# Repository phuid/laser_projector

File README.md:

# Raspberry Pi RGB laser projector
A vector laser projector with an easy to understand UI.\
UI includes:
- integrated display control with a rotary encoder,
- web server on the local network
- discord bot accesible when the RPi is online

## table of contents
- [Raspberry Pi RGB laser projector](#raspberry-pi-rgb-laser-projector)
  - [table of contents](#table-of-contents)
  - [thesis](#thesis)
  - [how to install](#how-to-install)
  - [supported projection file formats](#supported-projection-file-formats)
  - [hw](#hw)
    - [galvos](#galvos)
      - [DAC - mcp4822](#dac---mcp4822)
      - [amps - TL082](#amps---tl082)
    - [laser](#laser)
    - [LCD + encoder](#lcd--encoder)
  - [sw](#sw)
    - [communication](#communication)
    - [lasershow](#lasershow)
    - [UI](#ui)
    - [web\_ui](#web_ui)
    - [discord\_bot](#discord_bot)
    - [wifi\_manager](#wifi_manager)
    - [comms format](#comms-format)
      - [lasershow comms](#lasershow-comms)
        - [basic commands:](#basic-commands)
        - [responses:](#responses)
      - [wifi\_manager comms](#wifi_manager-comms)

## thesis
I wrote a whole thesis in [czech](https://en.wikipedia.org/wiki/Czech_Republic) language about this project. It is available in [this repository](https://github.com/phuid/laser_projector-thesis) [(direct link to the pdf file)](https://github.com/phuid/laser_projector-thesis/blob/master/text.pdf).

## how to install

```bash
git clone https://github.com/phuid/laser_projector.git
cd laser_projector
bash install.sh
```
this script installs all the dependencies of my programs and sets up the RaspberryPi to start all the programs on boot using [pm2](https://pm2.keymetrics.io/).

## supported projection file formats
The projector can read and project **.ild** and (much more popular) **.svg** file formats.
**.ild** files can be generated using specialised software like [laserworld showeditor](https://www.showeditor.com/en).
**.svg** files from any editor are internally converted to **.ild** using [this svg2ild.py script](https://github.com/marcan/openlase/blob/master/tools/svg2ild.py) from [gh/marcan/openlase](https://github.com/marcan/openlase)

## hw
My plans include battery power, usually galvos come with a power supply and powering the laser isn't that hard using a step-up. My module takes around 0.45A @ 9V. Make sure you dont brick your pi by taking its power. Raspberry Pis often don't take it well when an undervoltage occurs on their 5V line and they certainly aren't made to power anything more than an LED from their 3.3V PS.

### galvos
take -10 to +10V differential signal between to lines (base and inverted),
The DAC + opamps circuit which generates this signal is nicely described in [this article](https://www.instructables.com/Arduino-Laser-Show-With-Real-Galvos/).
My implemetation of it in kicad files can be found in [pcb/kicad](pcb/kicad).

#### DAC - mcp4822
DAC controlled by the RPi creates an analog signal between 0 and 5V.

#### amps - TL082
TL082 from texas instruments, each channel has one chip, each chip has two op amps.
One opamp inverts and modifies the signal based on the potenciometers (getting the inverted ILDA signal),
Second opamp inverts it again for the base ILDA signal

### laser
rgb laser module from https://www.laserlands.net/diode-laser-module/rgb-combined-white-laser-module/11010003.html
requires 8.5-12V power
takes 35kHz TTL / PWM on 3 pins, these pins are connected directly to the raspberry pi

pin connections between the laser module and RPi
|LASER|RPi|
|---|---|
|red|GPIO22|
|green|GPIO27|
|blue|GPIO17|

### LCD + encoder
Any 20x4 LCD with an I2C backpack + any rotary encoder with a button 
LCD connections:
|LCD|RPi|
|---|---|
|Vcc|5V|
|GND|GND|
|SCK|GPIO3|
|SDA|GPIO2|
|backlight|GPIO18|

encoder connections:
|encoder|RPi|
|---|---|
|A|GPIO5|
|common|GND|
|B|GPIO6|
|button1|GND|
|button1|GPIO13|

## sw
2 backend programs (lasershow *(c++)* + wifi_manager *(node.js)*) and 3 frontend programs (UI *(c++)* + web_ui *(node.js)* + discord_bot *(node.js)*)

### communication
each backend has its pub/sub sockets
lasershow publishes to `tcp://localhost:5556` and receives commands from `tcp://localhost:5556`
wifi_manager publishes to `tcp://localhost:5558` and receives commands from `tcp://localhost:5559`

### lasershow
- backend program that takes care of the actual projecting through controlling the galvos and the laser module

### UI
- allows control of backend programs through the built-in LCD and encoder

### web_ui
- allows control of backend programs through a web interface available on the local network

### discord_bot
- allows control of backend programs through a discord bot

### wifi_manager
- allows switching between three modes of wifi:
  - wifi off (`stealth`)
  - wifi on (`wifi`) -- RPi wifi on and trying to connect to known nearby networks
  - access point (`hotspot`) -- RPi wifi on transmitting its own wifi which other devices can connect to

### comms format
#### lasershow comms

lasershow executable takes commands **from all UI processes** through a **ZeroMQ TCP socket**
command format
`COMMAND` + ` ` + `ARG1` + ` ` + `ARG2` + ` ` + ` ` + `ARG4`
-> parse with a simple while loop lol no need for fancy functions

##### basic commands:
any process can send a command into the socket and all processes will read responses from lasershow executable
- `PROJECT` args: `<filename>`
  - `<filename>` must have extension `.ild`<!-- or `.lpc`(laserprojector_custom) --> otherwise error `INVALID_ARG`
- `STOP` (no args)
- `PAUSE` (no args)
- `GAME` args: `<game_name>`
  - `game_name` is any of the following ``//TODO: game names (not yes implemented)
- `PRESS` (no args), only handled if game is running
- `RELEASE` (no args), only handled if game is running
- `OPTION` args: `<mode>` `<option_name>` `<value>`
  - `mode`: any of `write`/`read`/`reset`
  - `option_name`: any of the following
    - `progress`
    - `current_frame` - if a projection is active, this will seek to the defined frame of the projection, must not exceed number_of_frames (every pos info gives this argument)
    - `point_delay`
    - `target_frame_time`
    - `repeat`
    - `trapeziod_horizontal`
    - `trapeziod_vertical`
  - `value` only read when using `write` parameter

##### responses:
lasershow exec can write to the socket at any time
- `ERROR: <e> <details>`:
  - `e`: any of the following; returned if received command couldn't be parsed correctly
    - `E2BIG`: too many arguments (option read/reset command probably includes value argument)
    - `EINVAL`: invalid argument (typo in argument or project filename probably has wrong extension)
    - `ENOENT`: file doesn't exist
    - `INVALID_CMD`: probably typo in a command
    - `OTHER`
  - `details`: if error type supports it, details will be included
- there is no success message
- `INFO: <details>`
  - details - one of following:
    - `OPTION <name> <val>`
      - name: name of option being changed; *any of*:
        - `point_delay`
        - `repeat`
        - `target_frame_time`
        - `trapezoid_horizontal`
        - `trapezoid_vertical`
      - val: numeric (float) value of the option
    - `STOP`
    - `PAUSE <val>`
      - val: 1 - paused, 0 - not paused
    - `PROJECT <filename>`
      - filename: filename of the file being projected
    - `POS <pos> OF <max>`
      - pos: position of coursor in projected file
      - max: size of projected file
- `DISPLAY: <text>`: client shall display text to the user and hide it when a new command comes or when user sees it
- `ALERT: <text>`: client shall display text to the user and only hide it and process following commands after user sees the alert

#### wifi_manager comms
takes following commands
- `read`: prints out following parameters:
  - `wifi_setting: <stealth|wifi|hotspot>`
  - `wifi_ssid: <SSID>`: SSID as returned by `iwgetid --raw` or `iw dev` in case hotspot is active
  - `mode_raw: <MODE_RAW>`: MODE_RAW (0-7) as returned by `iwgetid --mode --raw`
  - `mode: <MODE>`: MODE based on MODE_RAW; possible outputs: `Auto|Ad-Hoc|Managed|Master|Repeater|Secondary|Monitor|Unknown/bug`

- `write <stealth|wifi|hotspot>`
  - `stealth`: wifi off
  - `wifi`: connect to nearby known networks
  - `hotspot`: create new network, raspberry pi becomes the access point

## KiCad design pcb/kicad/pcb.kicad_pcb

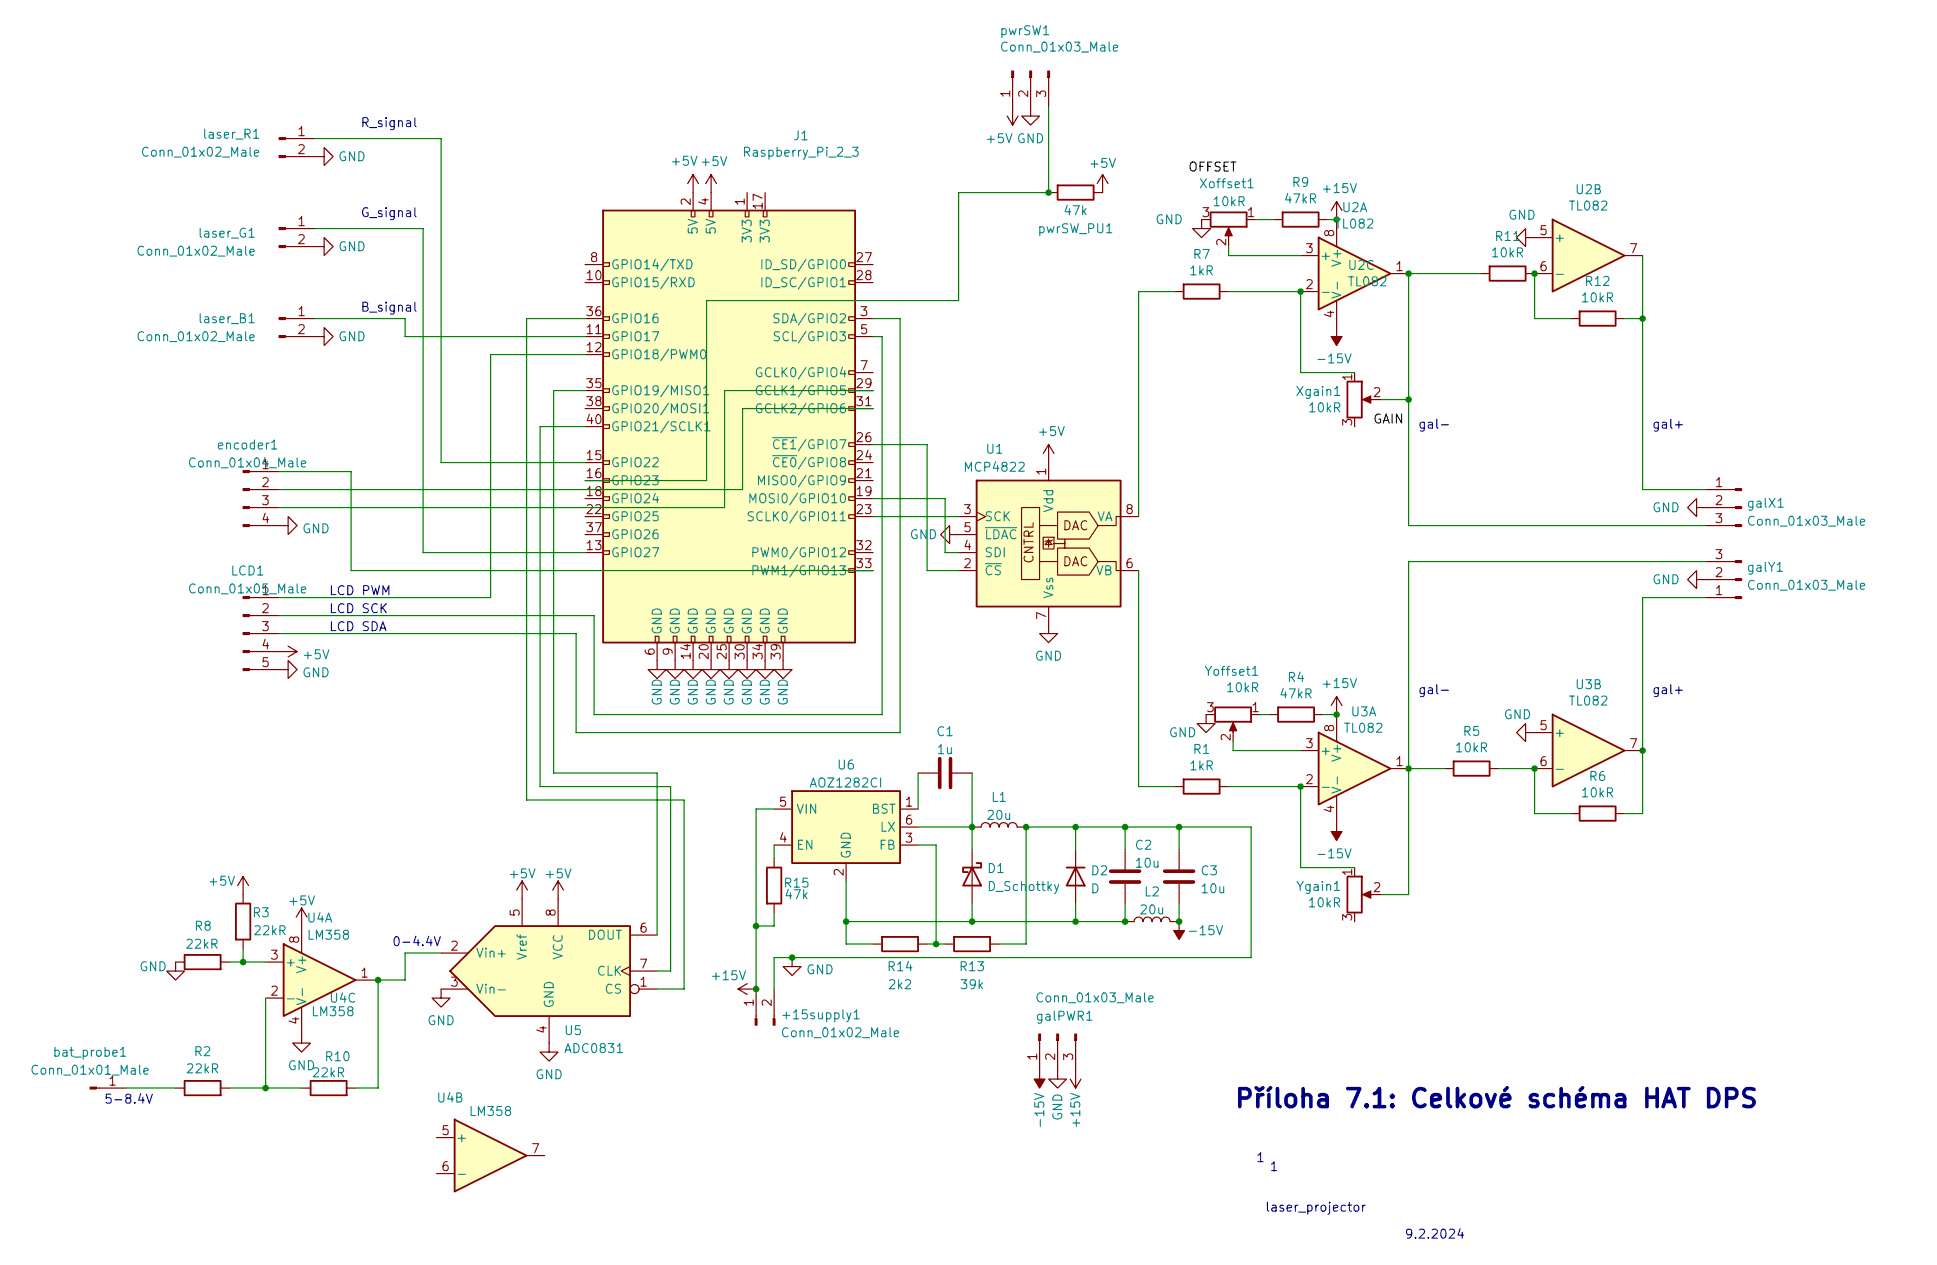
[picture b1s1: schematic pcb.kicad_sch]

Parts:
+15supply1: Conn_01x02_Male; PinHeader_1x02_P2.54mm_Horizontal
C1: 1u; C_Disc_D5.0mm_W2.5mm_P5.00mm
C2, C3: 10u; CP_Radial_D5.0mm_P2.00mm
D1: D_Schottky; D_SMC_Handsoldering
D2: D; D_SMC_Handsoldering
J1: Raspberry_Pi_2_3; PinSocket_2x20_P2.54mm_Vertical
L1, L2: 20u; L_Sumida_CR75
LCD1: Conn_01x05_Male; PinHeader_1x05_P2.54mm_Horizontal
R1, R7: 1kR; R_1812_4532Metric_Pad1.30x3.40mm_HandSolder
R2, R3, R8, R10: 22kR; R_1812_4532Metric_Pad1.30x3.40mm_HandSolder
R4, R9: 47kR; R_1812_4532Metric_Pad1.30x3.40mm_HandSolder
R5, R6, R11, R12: 10kR; R_1812_4532Metric_Pad1.30x3.40mm_HandSolder
R13: 39k; R_1812_4532Metric_Pad1.30x3.40mm_HandSolder
R14: 2k2; R_1812_4532Metric_Pad1.30x3.40mm_HandSolder
R15: 47k; R_1812_4532Metric_Pad1.30x3.40mm_HandSolder
U1: MCP4822; DIP-8_W7.62mm
U2, U3: TL082; DIP-8_W7.62mm
U4: LM358; DIP-8_W7.62mm
U5: ADC0831; DIP-8_W7.62mm
U6: AOZ1282CI; SOT-23-6
Xgain1: 10kR; Potentiometer_Alps_RK09K_Single_Vertical
Xoffset1: 10kR; Potentiometer_Alps_RK09K_Single_Vertical
Ygain1: 10kR; Potentiometer_Alps_RK09K_Single_Vertical
Yoffset1: 10kR; Potentiometer_Alps_RK09K_Single_Vertical
bat_probe1: Conn_01x01_Male; PinHeader_1x01_P2.54mm_Horizontal
encoder1: Conn_01x04_Male; PinHeader_1x04_P2.54mm_Horizontal
galPWR1: Conn_01x03_Male; PinHeader_1x03_P2.54mm_Horizontal
galX1: Conn_01x03_Male; PinHeader_1x03_P2.54mm_Horizontal
galY1: Conn_01x03_Male; PinHeader_1x03_P2.54mm_Horizontal
laser_B1: Conn_01x02_Male; PinHeader_1x02_P2.54mm_Horizontal
laser_G1: Conn_01x02_Male; PinHeader_1x02_P2.54mm_Horizontal
laser_R1: Conn_01x02_Male; PinHeader_1x02_P2.54mm_Horizontal
pwrSW1: Conn_01x03_Male; PinHeader_1x03_P2.54mm_Horizontal
pwrSW_PU1: 47k; R_1812_4532Metric_Pad1.30x3.40mm_HandSolder

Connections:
+5V: J1.2 (5V), J1.4 (5V), LCD1.4, R3.1, U1.1 (Vdd), U4.8 (V+), U5.5 (Vref), U5.8 (VCC), pwrSW1.1, pwrSW_PU1.1
+15V: +15supply1.1, R4.1, R9.1, R15.2, U2.8 (V+), U3.8 (V+), U6.5 (VIN), galPWR1.3
-15V: C3.2, L2.2, U2.4 (V-), U3.4 (V-), galPWR1.1
GND: +15supply1.2, C2.1, C3.1, D2.1 (K), J1.6 (GND), J1.9 (GND), J1.14 (GND), J1.20 (GND), J1.25 (GND), J1.30 (GND), J1.34 (GND), J1.39 (GND), L1.2, LCD1.5, R8.1, R13.1, U1.5 (~LDAC), U1.7 (Vss), U2.5 (+), U3.5 (+), U4.4 (V-), U5.3 (Vin-), U5.4 (GND), Xoffset1.3, Yoffset1.3, encoder1.4, galPWR1.2, galX1.2, galY1.2, laser_B1.2, laser_G1.2, laser_R1.2, pwrSW1.2
unnamed: C2.2, D1.2 (A), D2.2 (A), L2.1, R14.2, U6.2 (GND)
unnamed: C1.1, D1.1 (K), L1.1, U6.6 (LX)
unnamed: J1.29 (GCLK1/GPIO5), encoder1.3
unnamed: J1.31 (GCLK2/GPIO6), encoder1.2
unnamed: J1.36 (GPIO16), U5.1 (CS)
unnamed: J1.11 (GPIO17), laser_B1.1
unnamed: J1.12 (GPIO18/PWM0), LCD1.1
unnamed: J1.35 (GPIO19/MISO1), U5.6 (DOUT)
unnamed: J1.40 (GPIO21/SCLK1), U5.7 (CLK)
unnamed: J1.15 (GPIO22), laser_R1.1
unnamed: J1.16 (GPIO23), pwrSW1.3, pwrSW_PU1.2
unnamed: J1.13 (GPIO27), laser_G1.1
unnamed: J1.19 (MOSI0/GPIO10), U1.4 (SDI)
unnamed: J1.33 (PWM1/GPIO13), encoder1.1
unnamed: J1.23 (SCLK0/GPIO11), U1.3 (SCK)
unnamed: J1.5 (SCL/GPIO3), LCD1.2
unnamed: J1.3 (SDA/GPIO2), LCD1.3
unnamed: J1.26 (~CE1/GPIO7), U1.2 (~CS)
unnamed: R4.2, Yoffset1.1
unnamed: R9.2, Xoffset1.1
unnamed: R7.2, U1.8 (VA)
unnamed: R1.2, U1.6 (VB)
unnamed: U2.3 (+), Xoffset1.2
unnamed: R7.1, U2.2 (-), Xgain1.1
unnamed: R11.1, R12.2, U2.6 (-)
unnamed: U3.3 (+), Yoffset1.2
unnamed: R1.1, U3.2 (-), Ygain1.1
unnamed: R5.1, R6.2, U3.6 (-)
unnamed: R3.2, R8.2, U4.3 (+)
unnamed: R2.2, R10.1, U4.2 (-)
unnamed: R10.2, U4.1, U5.2 (Vin+)
unnamed: C1.2, U6.1 (BST)
unnamed: R15.1, U6.4 (EN)
unnamed: R13.2, R14.1, U6.3 (FB)
unnamed: R2.1, bat_probe1.1
unnamed: R12.1, U2.7, galX1.1
unnamed: R11.2, U2.1, Xgain1.2, galX1.3
unnamed: R6.1, U3.7, galY1.1
unnamed: R5.2, U3.1, Ygain1.2, galY1.3

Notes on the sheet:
Příloha 7.1: Celkové schéma HAT DPS
LCD SCK
G_signal
0-4.4V
LCD PWM
gal-
9.2.2024
B_signal
LCD SDA
laser_projector
R_signal
gal+
5-8.4V

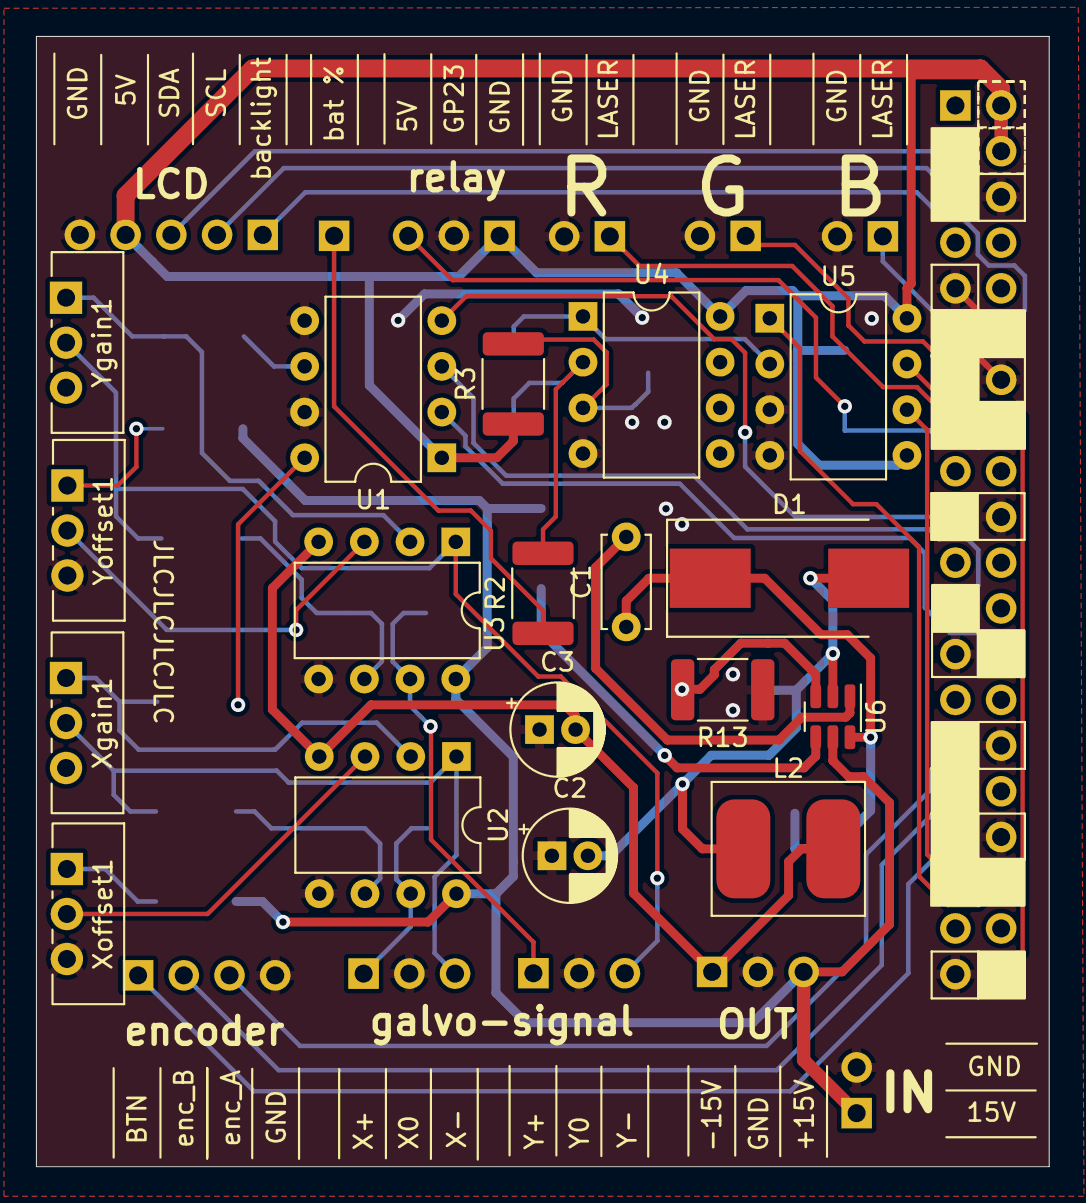
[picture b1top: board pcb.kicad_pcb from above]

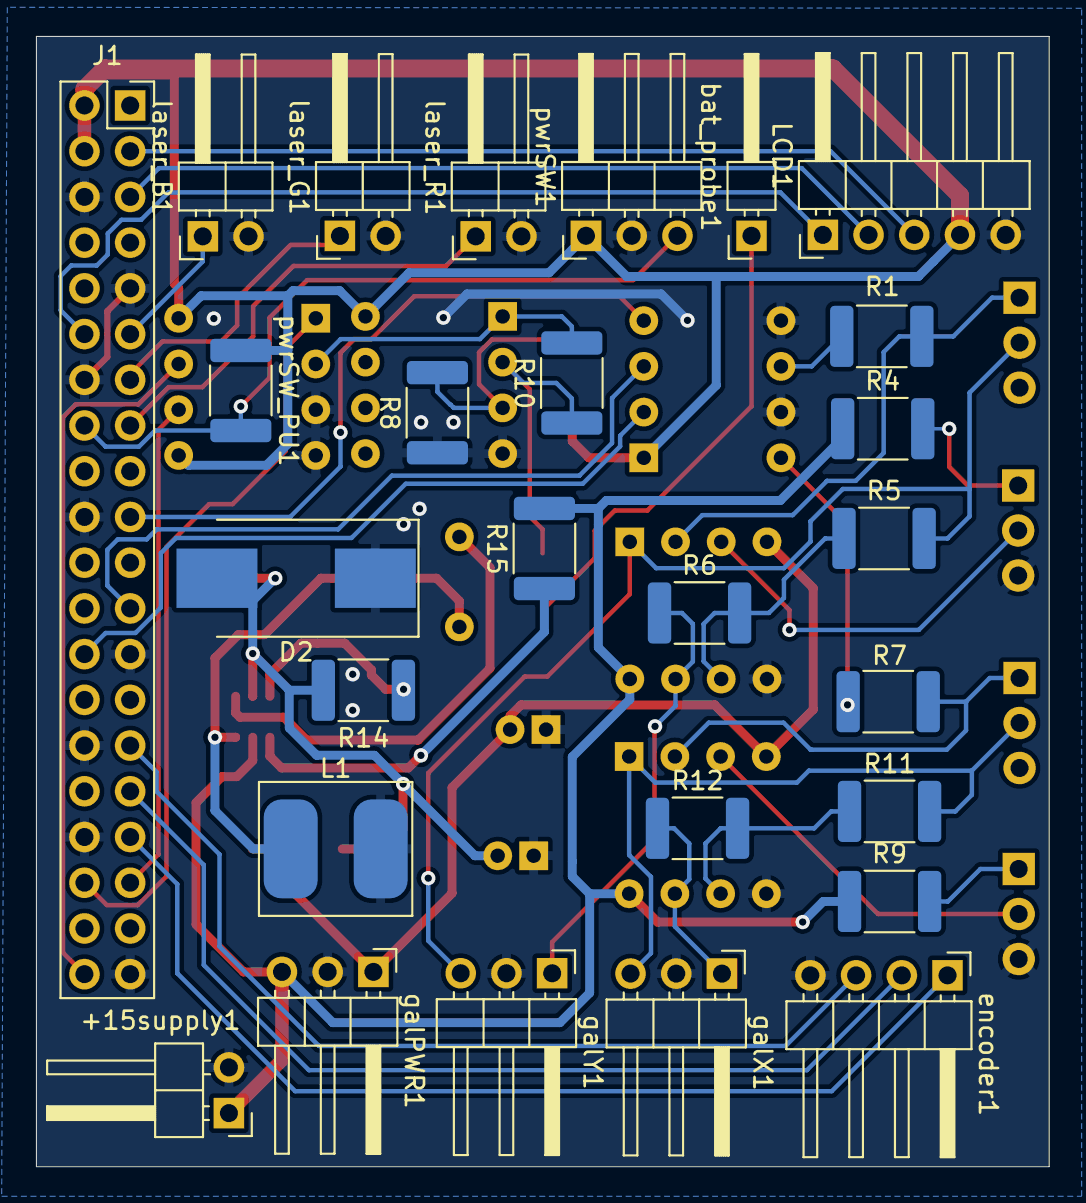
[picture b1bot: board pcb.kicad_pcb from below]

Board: 2 copper layers, 56.3 x 62.8 mm, 45 parts (27 on the bottom side), 43 nets.

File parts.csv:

### Footprint positions - created on Fri Jan 26 19:06:12 2024 ###,,,,,,,
### Printed by KiCad version 7.0.10,,,,,,,
## Unit = mm, Angle = deg.,,,,,,
## Side : both lol,,,,,,,
Ref, Val, Link, Package, PosX, PosY, Rot, Side
C1, 1u, https://www.gme.cz/v/1486151/hitano-ck-1u-50v-x7r-rm508-10-k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, C_Disc_D5.0mm_W2.5mm_P5.00mm,258.572,-54.3668,90, top
C2, 10u,https://www.gme.cz/v/1489492/hitano-ce-10u-63vit-hit-exr-5x1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, CP_Radial_D5.0mm_P2.00mm,254.4419,-67.0814,0, top
C3, 10u,, CP_Radial_D5.0mm_P2.00mm,253.7561,-60.071,0, top
D1, D_Schottky, https://www.gme.cz/v/1493653/ss56c-schottkyho-dioda, D_SMC_Handsoldering,267.6398,-51.6636,0, top
D2, D,, D_SMC_Handsoldering,-267.6398,-51.6636,0, bottom
U1, MCP4822,bought, DIP-8_W7.62mm,248.3258,-44.9734,180, top
U2, TL082,bought, DIP-8_W7.62mm,249.1386,-61.5696,-90, top
U3, TL082,bought, DIP-8_W7.62mm,249.1032,-49.6416,-90, top
U4, LM358,https://www.gme.cz/v/1487661/texas-instruments-lm358p, DIP-8_W7.62mm,256.169,-37.1194,0, top
U5, ADC0831,https://www.gme.cz/v/1490502/texas-instruments-adc0831ccn-nopb, DIP-8_W7.62mm,266.5476,-37.221,0, top
U6, AOZ1282CI,https://www.tme.eu/cz/en/details/aoz1282ci/voltage-regulator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, SOT-23-6,270.05,-59.3598,-90, top
J1, Raspberry_Pi_2_3,bought, PinSocket_2x20_P2.54mm_Vertical,-276.86,-25.4,180, bottom
L1, 20u,https://www.gme.cz/v/1496226/da105np-220m-tlumivka-smd, L_Sumida_CR75,-265.4446,-66.7004,180, bottom
L2, 20u,, L_Sumida_CR75,267.5782,-66.7004,0, top
R2, R,https://www.gme.cz/v/1485408/yageo-r1206-22k-025w-1-smd-rezistor, R_1812_4532Metric_Pad1.30x3.40mm_HandSolder,253.9492,-52.5018,90, top
R3, R,, R_1812_4532Metric_Pad1.30x3.40mm_HandSolder,252.2982,-40.8686,90, top
R8, R,, R_1812_4532Metric_Pad1.30x3.40mm_HandSolder,-259.7912,-42.4688,90, bottom
R10, R,, R_1812_4532Metric_Pad1.30x3.40mm_HandSolder,-252.3236,-40.8178,90, bottom
R13, 39k,https://www.gme.cz/v/1485560/yageo-r1206-39k-025w-1-smd-rezistor, R_1812_4532Metric_Pad1.30x3.40mm_HandSolder,263.9314,-57.8612,180, top
R1, 1kR,https://www.gme.cz/v/1485383/yageo-r1206-1k-025w-1-smd-rezistor, R_1812_4532Metric_Pad1.30x3.40mm_HandSolder,-235.1024,-38.227,0, bottom
R7, 1kR,, R_1812_4532Metric_Pad1.30x3.40mm_HandSolder,-234.7468,-58.5216,0, bottom
R4, 47kR,https://www.gme.cz/v/1483907/yageo-r1206-47k-025w-1-smd-rezistor, R_1812_4532Metric_Pad1.30x3.40mm_HandSolder,-235.0516,-43.3578,180, bottom
R9, 47kR,, R_1812_4532Metric_Pad1.30x3.40mm_HandSolder,-234.6706,-69.6214,180, bottom
R15, 47kR,, R_1812_4532Metric_Pad1.30x3.40mm_HandSolder,-253.8476,-50.0126,90, bottom
pwrSW_PU1, 47kR,, R_1812_4532Metric_Pad1.30x3.40mm_HandSolder,-270.7132,-41.2344,-90, bottom
R5, 10kR,https://www.gme.cz/v/1486609/yageo-r1206-10k-025w-1-smd-rezistor, R_1812_4532Metric_Pad1.30x3.40mm_HandSolder,-234.9754,-49.4538,180, bottom
R6, 10kR,, R_1812_4532Metric_Pad1.30x3.40mm_HandSolder,-245.227,-53.594,180, bottom
R11, 10kR,, R_1812_4532Metric_Pad1.30x3.40mm_HandSolder,-234.6706,-64.6176,180, bottom
R12, 10kR,, R_1812_4532Metric_Pad1.30x3.40mm_HandSolder,-245.34,-65.5574,180, bottom
R14, 2k2,https://www.gme.cz/v/1496462/yageo-r1206-2k2-025w-1-smd-rezistor, R_1812_4532Metric_Pad1.30x3.40mm_HandSolder,-263.906,-57.8866,0, bottom
Xgain1, 10kR,bought (may be burned), Potentiometer_Alps_RK09K_Single_Vertical,227.4504,-57.2362,0, top
Xoffset1, 10kR,, Potentiometer_Alps_RK09K_Single_Vertical,227.5266,-67.7264,0, top
Ygain1, 10kR,, Potentiometer_Alps_RK09K_Single_Vertical,227.4504,-36.078,0, top
Yoffset1, 10kR,, Potentiometer_Alps_RK09K_Single_Vertical,227.4758,-46.5428,0, top
bat_probe1, Conn_01x01_Male,bought (robotarna lol), PinHeader_1x01_P2.54mm_Horizontal,-242.3414,-32.639,90, bottom
encoder1, Conn_01x04_Male,, PinHeader_1x04_P2.54mm_Horizontal,-231.4508,-73.7266,-90, bottom
galPWR1, Conn_01x03_Male,, PinHeader_1x03_P2.54mm_Horizontal,-263.3472,-73.533,-90, bottom
galX1, Conn_01x03_Male,, PinHeader_1x03_P2.54mm_Horizontal,-243.982,-73.6284,-90, bottom
galY1, Conn_01x03_Male,, PinHeader_1x03_P2.54mm_Horizontal,-253.4158,-73.6092,-90, bottom
laser_B1, Conn_01x02_Male,, PinHeader_1x02_P2.54mm_Horizontal,-272.8264,-32.6706,90, bottom
laser_G1, Conn_01x02_Male,, PinHeader_1x02_P2.54mm_Horizontal,-265.2064,-32.6452,90, bottom
laser_R1, Conn_01x02_Male,, PinHeader_1x02_P2.54mm_Horizontal,-257.6626,-32.6706,90, bottom
pwrSW1, Conn_01x03_Male,, PinHeader_1x03_P2.54mm_Horizontal,-251.5362,-32.639,90, bottom
LCD1, Conn_01x05_Male,, PinHeader_1x05_P2.54mm_Horizontal,-238.379,-32.5882,90, bottom
+15supply1, Conn_01x02_Male,, PinHeader_1x02_P2.54mm_Horizontal,-271.3736,-81.3816,0, bottom

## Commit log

2021-12-13 gyrec.svg update
2021-12-13 pcb design lvl1
2021-12-13 cloned https://github.com/tteskac/rpi-lasershow
2021-12-13 pcb half done
2021-12-15 learned how to convert 0-5v to (-10)-(+10)V
2021-12-18 node webui on localhost:5000
2021-12-18 nodejs webui complete
2021-12-18 stupid mistake fix
2021-12-20 figma pcb designs update
2021-12-20 pcb design exported to svg and png
2021-12-29 progress
2021-12-30 wifi manager done
2021-12-30 /home/pi/laser-projector/etc-dnsmasq.conf backup
2021-12-30 etc-hostapd.conf backup
2021-12-31 discord bot started
2022-01-01 started discord bot
2022-01-01 progress on dc bot
2022-01-02 wifi_manager fix
2022-01-02 webui sellect text onclick of textarea
2022-01-02 dc bot fix
2022-01-02 started work on README.md
2022-01-02 readme update
2022-01-02 progress on readme.md
2022-01-02 fix img in readme
2022-01-02 add start dnsmasq to wifi_manager on wifi start + readme what happens when my code runs
2022-01-03 Update TODO
2022-01-03 readme progress
2022-01-04 small adjustments to repo
2022-01-04 css go brrr
2022-02-05 backup from pc before switching to ws
2022-04-13 wifi manager failsafe
2022-04-13 asdf
2022-04-13 new pcb measurements
2022-04-13 polished new pcb measurements
2022-05-03 failsafe, project last on stealth
2022-05-10 zujbkfuniczbxtv
2022-12-27 add web_ui ilda file select menu
2022-12-27 remove node modules
2022-12-27 selectmenu works
2022-12-28 change lasershow executable
2022-12-28 change lasershow exec
2022-12-28 random improvements
2022-12-28 add install script
2022-12-28 fuck
2022-12-30 rewrote wifi manager
2023-01-02 add logs on boot to HDMI
2023-08-18 some work on install script
2023-08-19 start rewriting lasershow to support RGB - define format
2023-09-06 start ildareader modification
2023-09-08 fix some errors
2023-09-15 Delete Unit hostapd.service is masked.
    idk how this file even appeared
2023-10-02 saw a yt vid lol :)
2023-10-05 BIG ZRDOJ added to sources.txt
2023-10-05 branch RGB -> no rgb support in master
2023-10-07 started work on UI
2023-10-08 separate encoder.h
2023-10-08 encoder fully supported
2023-10-08 encoder fully supported - fix typo
2023-10-08 menu struct begin
2023-10-08 more meun stuff
2023-10-09 menu advancements
2023-10-10 pc to rpi
2023-10-10 FIXED CHANGEVAL and som other things around menu
2023-10-11 add SCROLL
2023-10-11 todo
2023-10-12 perfect scroll
2023-10-12 move values to the right (padded from left side)
2023-10-12 about to implement selecting a value to change
2023-10-16 fix wiringpi install
2023-10-18 add sources
2023-10-19 more UI test text
2023-10-19 move img to laser_projector-thesis repo
2023-10-19 move tools & config templates to separate folders
2023-10-23 handle function button presses (not bouncing) +hostpad unit is masked something
2023-10-23 values handling finished
2023-10-23 debounce encoder button
2023-10-25 begin work on back button
2023-10-29 BACK BUTTON WOOOOOOOOO
2023-10-29 reposition comments at menu_interact() //redraw
2023-12-06 add selection on pc
2023-12-08 selection works, but still has bugs
2023-12-11 notes + new galvos
2023-12-11 rename UItest to UI
2023-12-11 rename UItest in makefile asw
2023-12-11 rename uitest in make file for real this time
2023-12-11 include fifo
2023-12-11 simpler menu function call
2023-12-12 commit to allow merge
2023-12-12 fully merge
2023-12-12 konzultace todos
2023-12-13 use references instead of pointers in menu.hpp
2023-12-13 use reference instead of pointer in a function call
2023-12-13 encoder to class - before compilation
2023-12-13 fix some errors, not all
2023-12-14 commit sace
2023-12-15 begin rollback -> without class static in cpp
2023-12-16 rewrite encoder.hpp without a class and add encoder.cpp with static variables
2023-12-16 install userauth default option & build folder gitignore
2023-12-16 fr this time
2023-12-16 Revert "Merge branch 'master' of https://github.com/phuid/laser-projector"
    This reverts commit 93da61a8a04ec3b4fb3066d637fb147b8a8e0b32, reversing
    changes made to 8b286b6aca0887c4bed6e5e3f5e220e789c5765d.
2023-12-16 todos
2023-12-16 konzult
2023-12-16 kozult asjdfh
2023-12-17 lasershow comm
2023-12-19 move to rpi3b
2023-12-19 selection dont crash
2023-12-19 readme sw requirements
2023-12-19 readme add wifi_manager
2023-12-21 isntall script zmq
2023-12-21 sync
2023-12-21 start work on zmq in lasershow exec
2023-12-22 lasershow tak file input
2023-12-22 move to zero
2023-12-22 found the bug
2023-12-23 comm work
2023-12-23 lasershow comm, start work on options
2023-12-23 options, cmake
2023-12-25 smth
2023-12-25 fix lasershow PROJECT command + UI comm
2023-12-26 save
2024-01-05 napajeni hw rozmyslene
2024-01-05 unite notes
2024-01-05 notes update
2024-01-05 update notes
2024-01-06 menu receive progress + patch val_redraw
2024-01-06 thesis uvod
2024-01-06 define responses in README
2024-01-06 define option names in readme
2024-01-06 fix readme typo
2024-01-06 menu finished
2024-01-06 menu patch
2024-01-07 menu comms fix final (hopefully)
2024-01-07 pcb, laser_screenshot
2024-01-07 napajeni update scheme
2024-01-07 napajeni update notes
2024-01-07 fix notes
2024-01-07 update notes - in progress RGB
2024-01-07 begin ildaReader RGB
2024-01-08 RGB ildareader
2024-01-08 RGB lasershow
2024-01-08 add files
2024-01-09 separate command header
2024-01-09 white square ilda file
2024-01-10 lasershow dont load file on repeat
2024-01-10 update seek spec
2024-01-10 ui custom command_names, seek prep
2024-01-10 fix lasershow errors
2024-01-10 UI fix errors
2024-01-10 lasershow brightness calc, pwm needed
2024-01-10 notes
2024-01-10 UI comms
2024-01-10 drzak na baterky
2024-01-12 fix bug - cleanup before repeat uninits everything and it isnt usable after
2024-01-14 todo install
2024-01-14 start pigpio
2024-01-14 lasershow pigpio
2024-01-14 UI pigpio
2024-01-14 Revert "UI pigpio"
    This reverts commit b01f6babbd70331cf5474e437a0bcbc8142a7693.
2024-01-14 UI back to wiringPi
2024-01-18 start updating web_ui for socket comms (3 terminals)
2024-01-18 idk som colors?
2024-01-18 UI repin
2024-01-19 pcb done
2024-01-21 pcb todo capacitors
2024-01-21 konzult pcb with tom
2024-01-22 smd pcb done
2024-01-22 rpi power pcb
2024-01-23 pigpio_UI
2024-01-25 begin transfer to lgpio (rpi5)
2024-01-25 libgpio before test
2024-01-26 finish lasershow lg transition
2024-01-26 lgpio UI
2024-01-27 gme & laskakit parts
2024-01-27 use gpiochip4 + gitignore cmake
2024-01-27 gitignore cmake
2024-01-28 ignore bin
2024-01-28 web UI landscape layout
2024-01-28 pcb silkscreen used pins
2024-01-28 web_ui ssh
2024-01-28 jlc order sent - pcb finished
2024-01-28 fix web_ui foreach terminal
2024-01-28 start web_ui swiper
2024-01-28 web_ui swiper
2024-01-29 add 3d models to kicad
2024-01-30 trapezoid mistake found
2024-02-02 pigpio lasershow + try trapezoid - still weird + rename helper file
2024-02-02 envelope comms, before lasershow rollback
2024-02-02 lasershow simpler multi receive
2024-02-02 web ui comms complete
2024-02-02 comms complete (on web_ui) with 4 sockets
2024-02-02 lasershow calculate points function
2024-02-02 lasershow option file saving
2024-02-03 web ui queue & settings overlay
2024-02-03 prezentace konzult
2024-02-03 lasershow pigpio delayMicros instead of usleep, laser_br calc note in cofig
2024-02-03 lasershow + UI - add "DISPLAY:" for notifications
2024-02-03 UI wiringpi
2024-02-03 UI DISPLAY: finished
2024-02-03 UI Alert
2024-02-03 alert in readme
2024-02-03 fix readme err string
2024-02-04 notes paid
2024-02-04 3d case,, notes botland paid
2024-02-04 to buy
2024-02-04 before chips to smlouva
2024-02-04 print smlouva
2024-02-04 lasershow scale_up
2024-02-04 recalculate points while projecting
2024-02-04 trapezoid WORKS
2024-02-05 filament ojednat
2024-02-05 web saturate
2024-02-05 weird
2024-02-05 fusion + nowplaying position fixed in landscape
2024-02-06 move, scale, seek, EXPAND COMMANDS (copilot's goated)
2024-02-07 vydaje++, 3d soubory
2024-02-10 some changes to lasershow
2024-02-10 more ls changes
2024-02-10 fix lasershow not receiving when projecting - before compile
2024-02-10 fix the fix
2024-02-11 ENCODER OVERSHOOT SOLVED?
2024-02-12 web ui settings
2024-02-12 UI options
2024-02-13 web webing
2024-02-14 settings fux
2024-02-15 bunch
2024-02-15 web styles
2024-02-15 UI wifiman
2024-02-15 last updateeasfas
2024-02-16 map ilda to resolution after transform
2024-02-16 fuuu
2024-02-16 revert the higher precision point calculation
2024-02-16 shutdown lcd
2024-02-16 proper scale ranges on web
2024-02-16 web shutdown
2024-02-16 UI load options
2024-02-16 lcd redraw on option receive
2024-02-17 UI dont eat CPU
2024-02-17 UI read bat voltage
2024-02-17 bat volt wow
2024-02-17 install instructions
2024-02-17 dont cleanup
2024-02-17 fix UI loop when pressed in display mode
2024-02-17 web stop
2024-02-18 pause resume time hop fixed
2024-02-18 debounce
2024-02-18 rm config
2024-02-18 readme toc
2024-02-18 web draw div
2024-02-19 go blue
2024-02-19 cool
2024-02-19 WIFI MANAGER WORKS
2024-02-23 Update README.md - LCD + enc connections
2024-02-23 toc in readme and stuff
2024-02-23 add pcb to git
2024-02-23 fix typo
2024-03-11 start web draw
2024-05-10 start draw
2024-05-22 discord bot
2024-05-22 git shenanigans
2025-05-27 how i found it after a year
2025-05-27 to pc
2025-05-27 how i found pc
2025-05-27 merg
2025-05-27 ilda-gen
2025-05-27 working ilda-gen
2025-05-31 functioning genLine
2025-05-31 letter
2025-05-31 letters
2025-06-21 TUNNEL
2025-06-22 HSV WORKs, tunnel
2026-01-19 licensing
